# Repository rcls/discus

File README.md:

Discus is an 8-bit CPU built from discrete transistors.
[Refer to the website for documentation](http://rcls.github.io/discus)

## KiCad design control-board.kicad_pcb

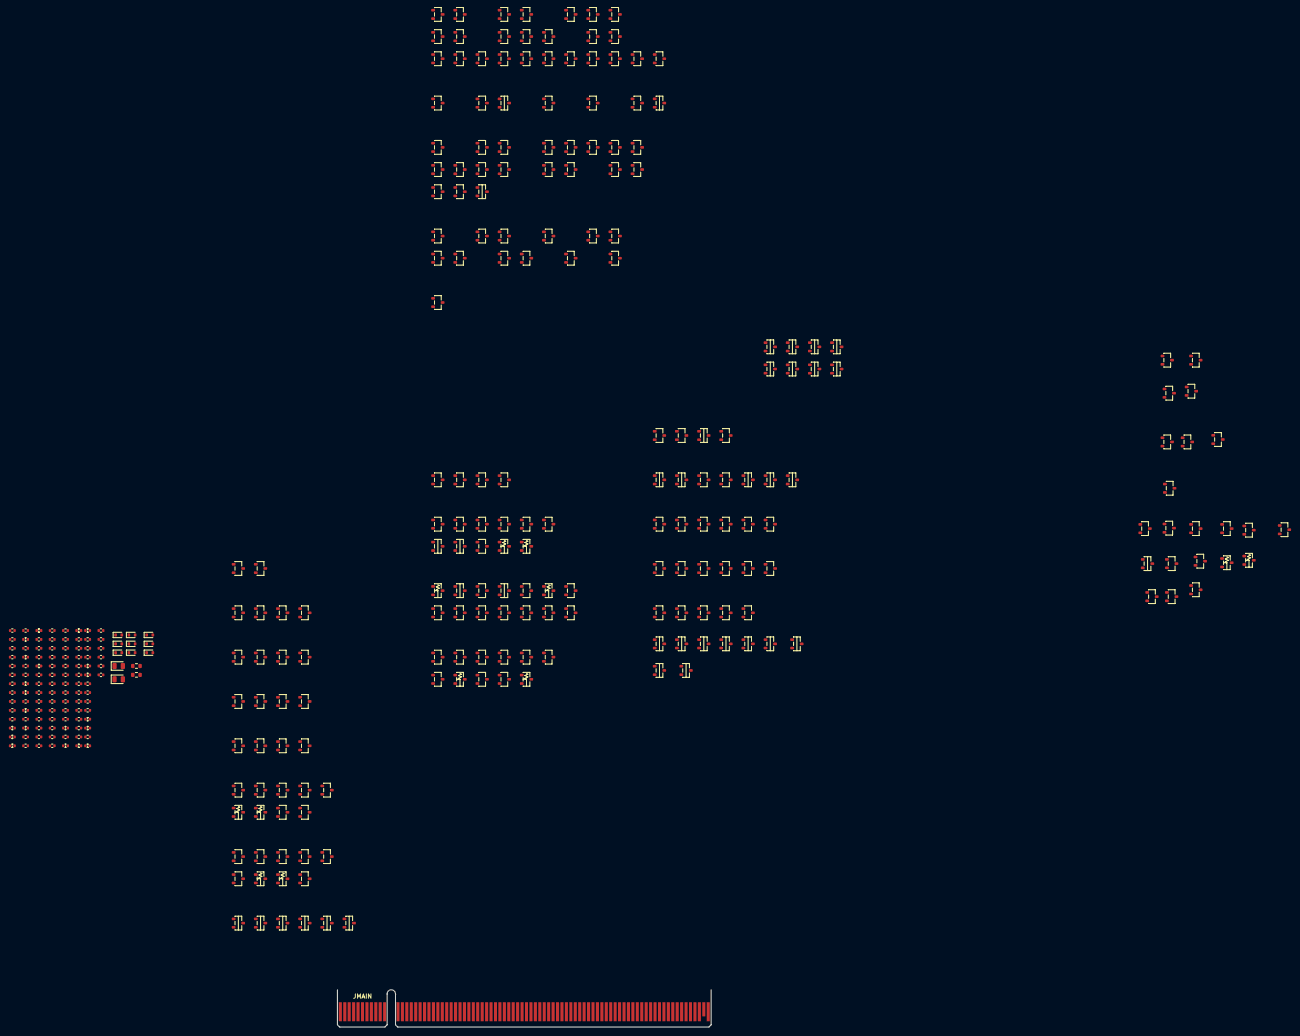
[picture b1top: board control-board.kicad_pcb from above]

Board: 4 copper layers, 331 parts (0 on the bottom side), 182 nets, no tracks yet.

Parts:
D0DS, D0W, D1DS, D1W, D2DS, D2W, D3DS, D3W, D4W: RB751S40; SOD523
D1: ledgreen; 0805-diode
D2: ledred; 0805-diode
JMAIN: unknown; BUS_PCIexpress_x16
M0DS, M0R, M0W, M1BJ, M1BK, M1DS, M1P, M1R, M1W, M2DS, M2N2, M2N4D, M2N7D, M2NP, M2P, M2PP, M2R, M2W, M3BJ, M3BK, M3DS, M3R, M3U6, M3W, M4DS, M4R, M4W, M5DS, M5R, M5W, M6R, M6W, M7R, M7W, M8W: NX3008PBK; SOT23_pmos
M1A1D, M1A2D, M1A3D, M1A4D, M1A5D, M1A6D, M1D, M1G, M1H, M1L2D, M1L4D, M1L5D, M1L6D, M1MAC, M1MAJ, M1MAK, M1MU5, M1MW1, M1MW2, M1N2, M1N4D, M1N7D, M1NAC, M1NAF0S, M1NAF1S, M1NAJ, M1NAK, M1NP, M1NU5, M1NW0, M1NW1, M1NW2, M1OL0S, M1OL1S, M1OU0S, M1OU1S, M1PP, M1S2D, M1S3D, M1S4D, M1S5D, M1S6D, M1S7D, M1U1, M1U2, M1U3, M1U6, M1U7, M2A1D, M2A2D, M2A3D, M2A4D, M2A5D, M2A6D, M2BJ, M2BK, M2D, M2G, M2H, M2L2D, M2L4D, M2L5D, M2L6D, M2MAC, M2MAJ, M2MAK, M2MU5, M2MW1, M2MW2, M2NAC, M2NAF0S, M2NAF1S, M2NAJ, M2NAK, M2NU5, M2NW0, M2NW1, M2NW2, M2OL0S, M2OL1S, M2OU0S, M2OU1S, M2S2D, M2S3D, M2S4D, M2S5D, M2S6D, M2S7D, M2U1, M2U2, M2U3, M2U6, M2U7, M3A2D, M3A5D, M3D, M3MAC, M3NAC, M3OU0S, M3OU1S, M3S3D, M3S4D, M3U3, M3U7, M4BJ, M4BK, M4D, M4S3D, M4S4D, M5D, M5S3D, M6D, M7D, M8D, M9D, M10D, M11D: FDV301N; SOT23_nmos
MAF0S, MAF1S: FDV301N; SOT23_nmos
MCD: FDV301N; SOT23_nmos
MIAC: FDV301N; SOT23_nmos
MIAF0S, MIAF1S: FDV301N; SOT23_nmos
MIAJ: FDV301N; SOT23_nmos
MIAK: FDV301N; SOT23_nmos
MIBC: FDV301N; SOT23_nmos
MIBF0S, MIBF1S: FDV301N; SOT23_nmos
MIP: NX3008PBK; SOT23_pmos
MIU5: FDV301N; SOT23_nmos
MIW0, MIW1, MIW2: FDV301N; SOT23_nmos
MJAC: FDV301N; SOT23_nmos
MJAF0S, MJAF1S: FDV301N; SOT23_nmos
MJAJ: FDV301N; SOT23_nmos
MJAK: FDV301N; SOT23_nmos
MJBC: FDV301N; SOT23_nmos
MJBF0S, MJBF1S: FDV301N; SOT23_nmos
MJU5: FDV301N; SOT23_nmos
MJW0, MJW1, MJW2: FDV301N; SOT23_nmos
ML0S, ML1D, ML1S, ML3D, ML7D, ML8D: FDV301N; SOT23_nmos
MN0, MN0S, MN1, MN1S, MN3D, MN5D, MN6D: FDV301N; SOT23_nmos
MNL0S, MNL1S: FDV301N; SOT23_nmos
MNU0S, MNU1S: FDV301N; SOT23_nmos
MS1D: FDV301N; SOT23_nmos
MS8D: NX3008PBK; SOT23_pmos
MU4: FDV301N; SOT23_nmos
MW0: FDV301N; SOT23_nmos
Q1BC, Q1BF0S, Q1BF1S, Q1BJ, Q1BK, Q1U6, Q2BC, Q2BF0S, Q2BF1S, Q2BJ, Q2BK, Q2U6: PDTC124TU; SOT23_bias
R0, R0DS, R0R, R0W, R1, R1DS, R1R, R1U6, R1W, R2, R2DS, R2R, R2U6, R2W, R3, R3DS, R3R, R3W, R4, R4R, R4W, R5, R6, R7: 2k49; R_0402_load
R1BJ, R1BK, R1D, R1P, R1S3D, R2BJ, R2BK, R2P, R2S3D, R3D, R4D: 820; R_0402_strong
R8, R9: 1k5; 0603
RA1D, RA2D, RA4D, RA6D: 2k49; R_0402_load
RCD: 2k49; R_0402_load
RG: 2k49; R_0402_load
RH: 2k49; R_0402_load
RIAC: 2k49; R_0402_load
RIAF0S, RIAF1S: 2k49; R_0402_load
RIAJ: 2k49; R_0402_load
RIAK: 2k49; R_0402_load
RIBC: 2k49; R_0402_load
RIBF0S, RIBF1S: 2k49; R_0402_load
RIP: 2k49; R_0402_load
RIU5: 2k49; R_0402_load
RIW0, RIW1, RIW2: 2k49; R_0402_load
RJAC: 2k49; R_0402_load
RJAF0S, RJAF1S: 2k49; R_0402_load
RJAJ: 2k49; R_0402_load
RJAK: 2k49; R_0402_load
RJBC: 2k49; R_0402_load
RJBF0S, RJBF1S: 2k49; R_0402_load
RJU5: 2k49; R_0402_load
RJW0, RJW1, RJW2: 2k49; R_0402_load
RL0S, RL1S, RL2D: 820; R_0402_strong
RL1D, RL3D, RL4D, RL7D, RL8D: 2k49; R_0402_load
RMAC: 2k49; R_0402_load
RMAJ: 2k49; R_0402_load
RMAK: 2k49; R_0402_load
RMU5: 2k49; R_0402_load
RMW1, RMW2: 2k49; R_0402_load
RN0, RN1, RN3D, RN5D, RN6D: 2k49; R_0402_load
RN0S, RN1S: 820; R_0402_strong
RNL0S, RNL1S: 820; R_0402_strong
RNU0S, RNU1S: 2k49; R_0402_load
ROU0S, ROU1S: 2k49; R_0402_load
RS1D, RS5D, RS7D: 820; R_0402_strong
RS6D, RS8D: 2k49; R_0402_load
RU1, RU2, RU3, RU4, RU7: 2k49; R_0402_load

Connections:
AND: JMAIN.B60, M1A2D.3 (D), M1N7D.1 (G), M2A2D.3 (D), M2N7D.1 (G), M3A2D.3 (D), RA2D.1
AR#: JMAIN.B58, M1N4D.3 (D), M2N4D.3 (D)
AS: JMAIN.B59, M1A3D.3 (D), M2A3D.3 (D)
BK: M1BK.3 (D), M2BK.3 (D), M6R.1 (G), R1BK.1
BK#: M3BK.3 (D), M4BK.3 (D), M7R.1 (G), R2BK.2
Bling: D1.2, D2.2, JMAIN.B67
CON: JMAIN.B53, M1U2.1 (G), M1U3.3 (D), M2U3.3 (D), M3U3.3 (D), MU4.2 (S), RU3.1
CR: JMAIN.B55, M11D.3 (D)
CR#_D: M1A4D.1 (G), M1A6D.3 (D), M11D.1 (G), RA6D.1
CS#: JMAIN.B56, M1N7D.3 (D), M2N7D.3 (D)
CW#: M3MAC.1 (G), M3NAC.1 (G), MCD.3 (D), RCD.1
Ci#: JMAIN.B7, M1MAC.1 (G)
Co: M3D.1 (G), MIBC.1 (G), MJBC.3 (D), Q1BC.3, RJBC.1
Co#: M2S2D.1 (G), MIBC.3 (D), MJBC.1 (G), Q2BC.3, R8.1, RIBC.1
CoE#: JMAIN.B57, M1D.3 (D), M2D.3 (D), M8D.3 (D), R3D.1
Cond#_D: M1S5D.1 (G), M3S3D.3 (D), M4S4D.1 (G), R2S3D.1
D#_A_C: M1MAC.3 (D), M1NAC.1 (G), M2MAC.3 (D), M3MAC.3 (D), MIAC.2 (S), RMAC.1
D#_A_J: M1MAJ.3 (D), M1NAJ.1 (G), M2MAJ.3 (D), MIAJ.2 (S), RMAJ.1
D#_A_K: M1MAK.3 (D), M1NAK.1 (G), M2MAK.3 (D), MIAK.2 (S), RMAK.1
D#_U5: M1MU5.3 (D), M1NU5.1 (G), M2MU5.3 (D), MIU5.2 (S), RMU5.1
D#_W1: M1MW1.3 (D), M1NW1.1 (G), M2MW1.3 (D), MIW1.2 (S), RMW1.1
D#_W2: M1MW2.3 (D), M1NW2.1 (G), M2MW2.3 (D), MIW2.2 (S), RMW2.1
Flag_D: M1S2D.3 (D), M1S3D.1 (G), M4S3D.1 (G), MS1D.3 (D), RS1D.1
GND: JMAIN.B34, M1A2D.2 (S), M1A3D.2 (S), M1A4D.2 (S), M1D.2 (S), M1L2D.2 (S), M1MAC.2 (S), M1MAJ.2 (S), M1MAK.2 (S), M1MU5.2 (S), M1MW1.2 (S), M1MW2.2 (S), M1N2.2 (S), M1N4D.2 (S), M1N7D.2 (S), M1NAC.2 (S), M1NAF0S.2 (S), M1NAF1S.2 (S), M1NAJ.2 (S), M1NAK.2 (S), M1NP.2 (S), M1NU5.2 (S), M1NW0.2 (S), M1NW1.2 (S), M1NW2.2 (S), M1OL0S.2 (S), M1OL1S.2 (S), M1OU0S.2 (S), M1OU1S.2 (S), M1PP.2 (S), M1S4D.2 (S), M1S5D.2 (S), M1S6D.2 (S), M1U1.2 (S), M1U3.2 (S), M1U6.2 (S), M1U7.2 (S), M2A2D.2 (S), M2A3D.2 (S), M2A4D.2 (S), M2BJ.2 (S), M2BK.2 (S), M2H.2 (S), M2L2D.2 (S), M2MAC.2 (S), M2MAJ.2 (S), M2MAK.2 (S), M2MU5.2 (S), M2MW1.2 (S), M2MW2.2 (S), M2NAC.2 (S), M2NAF0S.2 (S), M2NAF1S.2 (S), M2NAJ.2 (S), M2NAK.2 (S), M2NU5.2 (S), M2NW0.2 (S), M2NW1.2 (S), M2NW2.2 (S), M2OL0S.2 (S), M2OL1S.2 (S), M2OU0S.2 (S), M2OU1S.2 (S), M2S2D.2 (S), M2S3D.2 (S), M2S4D.2 (S), M2S5D.2 (S), M2S6D.2 (S), M2S7D.2 (S), M2U1.2 (S), M2U2.2 (S), M2U3.2 (S), M2U6.2 (S), M2U7.2 (S), M3A2D.2 (S), M3MAC.2 (S), M3NAC.2 (S), M3S4D.2 (S), M3U3.2 (S), M4BJ.2 (S)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
I0: JMAIN.B17, M0R.1 (G), M2R.1 (G)
I0#: JMAIN.B18, M1R.1 (G), M3R.1 (G)
I1: JMAIN.B19, M4R.1 (G)
I1#: JMAIN.B20, M5R.1 (G)
I2: JMAIN.B21, M1A1D.1 (G), M1A5D.1 (G), M1L4D.1 (G), M8D.1 (G)
I2#: JMAIN.B22, M1A2D.1 (G), M1A3D.1 (G), M1A6D.1 (G), M5D.1 (G)
I3: JMAIN.B23, M2L4D.1 (G)
I3#: JMAIN.B24, M1L2D.1 (G), M2A2D.1 (G), M2A5D.1 (G), M2A6D.2 (S), M2D.1 (G), ML1D.1 (G), ML7D.1 (G)
I4: JMAIN.B25, M2A4D.1 (G), M4D.1 (G), ML8D.1 (G)
I4#: JMAIN.B26, M1G.1 (G), M9D.1 (G), ML3D.1 (G)
I5: JMAIN.B27, M1L6D.1 (G), M1MW1.1 (G)
I5#: JMAIN.B28, M1U7.1 (G), M2L5D.2 (S)
I6: JMAIN.B29, M1L5D.1 (G), M1U3.1 (G), M2U7.1 (G), M3A5D.2 (S), M6D.1 (G)
I6#: JMAIN.B30, M1L6D.2 (S), M2A1D.1 (G), M2A3D.1 (G), M2G.1 (G), M2L6D.2 (S), M7D.1 (G), M10D.1 (G), MCD.1 (G)
I7: JMAIN.B31, M2L6D.1 (G), M2U3.1 (G), M3U7.1 (G)
I7#: JMAIN.B32, M2L5D.1 (G), MCD.2 (S), MN5D.2 (S)
IJ: JMAIN.B68, M1A1D.2 (S), M1D.1 (G), M2A1D.2 (S), M3A2D.1 (G), M3BJ.3 (D), M3U3.1 (G), M4BJ.3 (D), MN6D.2 (S), R2BJ.2
IJ#: M1BJ.3 (D), M2A6D.1 (G), M2BJ.3 (D), M2H.1 (G), M3A5D.1 (G), M6R.2 (S), M7R.2 (S), R1BJ.1, R9.1
IN#: JMAIN.B63, ML7D.3 (D), RL7D.1
Inc: JMAIN.B1, M1S6D.3 (D), M2S6D.3 (D), RS6D.1
Jump: JMAIN.B2, M1S5D.3 (D), M1S7D.1 (G), M2S5D.3 (D), M2S6D.1 (G), RS5D.1
K6#: JMAIN.B51, MN0.3 (D), RN0.1
K7#: JMAIN.B52, MN1.3 (D), RN1.1
MPre#: ML7D.2 (S), ML8D.3 (D), MU4.1 (G), RL8D.1
MR#: JMAIN.B66, M1L4D.3 (D), MN5D.1 (G), RL4D.1
MW: JMAIN.B65, M1L2D.3 (D), M2L2D.3 (D), RL2D.1
Misc#_D: M1L5D.3 (D), ML3D.2 (S), ML8D.2 (S)
N#: JMAIN.B62, M1A5D.3 (D), R4D.2
O0: JMAIN.B9, MN0.1 (G), R0.1
O1: JMAIN.B10, MN1.1 (G), R1.1
O2: JMAIN.B11, M2S3D.1 (G), M5S3D.1 (G), R2.1
O3: JMAIN.B12, MS1D.1 (G), R3.1
O4: JMAIN.B13, M1S2D.1 (G), R4.1
O5: JMAIN.B14, M1S4D.1 (G), M2S7D.1 (G), R5.1
O6: JMAIN.B15, M1U1.1 (G), MN3D.1 (G), R6.1
O6#_D: M2S4D.1 (G), MN3D.3 (D), RN3D.1
O7: JMAIN.B16, M2U1.1 (G), M3S4D.1 (G), R7.1
OJump#: M1MAJ.1 (G), M1U2.3 (D), M2S5D.1 (G), RU2.1
OR: JMAIN.B61, M1A4D.3 (D), M2A4D.3 (D), RA4D.1
OUT#: JMAIN.B64, ML1D.3 (D), RL1D.1
P0#_S: M2OL0S.1 (G), MIBF0S.1 (G), MJBF0S.3 (D), Q1BF0S.3, RJBF0S.1
P0_S: MIBF0S.3 (D), MJBF0S.1 (G), MNL1S.2 (S), Q2BF0S.3, RIBF0S.1
P1#_S: M2OL1S.1 (G), MIBF1S.1 (G), MJBF1S.3 (D), MNL0S.2 (S), Q1BF1S.3, RJBF1S.1
P1_S: MIBF1S.3 (D), MJBF1S.1 (G), Q2BF1S.3, RIBF1S.1
PRE: M1MAK.1 (G), MU4.3 (D), RU4.1
Push#: M1S7D.3 (D), M2OU0S.1 (G), M2OU1S.1 (G), MNU0S.1 (G), MNU1S.1 (G), MS8D.1 (G), RS7D.1
Q0#_S: M1DS.1 (G), M1OU1S.1 (G), M3DS.1 (G), MN0S.3 (D), MNU0S.2 (S), RN0S.1
Q0_S: M0DS.1 (G), M2DS.1 (G), ML0S.3 (D), MN0S.1 (G), RL0S.1
Q1#_S: M5DS.1 (G), MN1S.3 (D), MNU1S.2 (S), RN1S.1
Q1_S: M1OU0S.1 (G), M4DS.1 (G), ML1S.3 (D), MN1S.1 (G), RL1S.1
QE: JMAIN.B54, MN6D.3 (D), RN6D.1
Q_A1_D: M1A1D.3 (D), M1N4D.1 (G), M2A1D.3 (D), M2N4D.1 (G), RA1D.1
Q_G: M1G.3 (D), M1H.1 (G), M2G.3 (D), RG.1
Q_H: M1H.3 (D), M1NW0.1 (G), MIW0.2 (S), MW0.3 (D), RH.1
Q_I_P: M1P.1 (G), MIP.3 (D), RIP.2
Q_L6_D: M1L6D.3 (D), M2L4D.2 (S), M2L6D.3 (D)
Q_N5_D: MN5D.3 (D), MN6D.1 (G), RN5D.1
Q_N_L0_S: ML0S.1 (G), MNL0S.3 (D), RNL0S.1
Q_N_L1_S: ML1S.1 (G), MNL1S.3 (D), RNL1S.1
Q_O_L0_S: M1OL0S.3 (D), M2OL0S.3 (D), ML0S.2 (S)
Q_O_L1_S: M1OL1S.3 (D), M2OL1S.3 (D), ML1S.2 (S)
Q_U1: M1U1.3 (D), M2U1.3 (D), M2U2.1 (G), RU1.1
R0_S: M1NAF0S.1 (G), M3OU0S.3 (D), MAF0S.3 (D), MIAF0S.2 (S), ROU0S.1
R1_S: M1NAF1S.1 (G), M3OU1S.3 (D), MAF1S.3 (D), MIAF1S.2 (S), ROU1S.1
RA: JMAIN.B39, M0R.3 (D), R0R.2
RK: JMAIN.B43, M7R.3 (D), R4R.2
RST#: JMAIN.B8, M1MU5.1 (G)
RU: JMAIN.B42, M3R.3 (D), R3R.2
RX: JMAIN.B40, M1R.3 (D), R1R.2
RY: JMAIN.B41, M2R.3 (D), R2R.2
R_C: MIAC.3 (D), MJAC.1 (G), Q1BC.2, RIAC.1
R_F0_S: MIAF0S.1 (G), MJAF0S.3 (D), Q1BF0S.2, RJAF0S.1
R_F1_S: MIAF1S.1 (G), MJAF1S.3 (D), Q1BF1S.2, RJAF1S.1
R_J: MIAJ.3 (D), MJAJ.1 (G), Q1BJ.2, RIAJ.1
R_K: MIAK.3 (D), MJAK.1 (G), Q1BK.2, RIAK.1
Ret: JMAIN.B3, M1OL0S.1 (G), M1OL1S.1 (G), M1S4D.3 (D), M1S6D.1 (G), M2S4D.3 (D), M3S4D.3 (D), M4S4D.3 (D), MNL0S.1 (G), MNL1S.1 (G), R1D.2
S0: D0DS.2, JMAIN.B35, M0DS.3 (D), R0DS.2
S1: D1DS.2, JMAIN.B36, M1DS.3 (D), R1DS.2
S2: D3DS.2, JMAIN.B37, M3DS.3 (D), R3DS.2
S3: D2DS.2, JMAIN.B38, M2DS.3 (D), R2DS.2
S#_P: M1PP.1 (G), M2P.3 (D), M2PP.1 (G), R2P.1
SO#_D: M2L2D.1 (G), ML1D.2 (S), ML3D.3 (D), RL3D.1
S_C: MIAC.1 (G), MJAC.3 (D), Q2BC.2, RJAC.1
S_F0_S: MIAF0S.3 (D), MJAF0S.1 (G), Q2BF0S.2, RIAF0S.1
S_F1_S: MIAF1S.3 (D), MJAF1S.1 (G), Q2BF1S.2, RIAF1S.1
S_J: MIAJ.1 (G), MJAJ.3 (D), Q2BJ.2, RJAJ.1
S_K: MIAK.1 (G), MJAK.3 (D), Q2BK.2, RJAK.1
S_P: M1NP.1 (G), M1P.3 (D), M2NP.1 (G), R1P.1
VPush: JMAIN.B4, MS8D.3 (D), RS8D.2
Vdd: JMAIN.B33, M1BJ.2 (S), M1BK.2 (S), M1P.2 (S), M2N2.2 (S), M2N4D.2 (S), M2N7D.2 (S), M2NP.2 (S), M2P.2 (S), M2PP.2 (S), M3BJ.2 (S), M3BK.2 (S), M3U6.2 (S), MIP.2 (S), R1D.1, R1S3D.2, R1U6.2, R2S3D.2, R3D.2, R4D.1, RA1D.2, RA2D.2, RA4D.2, RA6D.2, RCD.2, RG.2, RH.2, RIAC.2, RIAF0S.2, RIAF1S.2, RIAJ.2, RIAK.2, RIBC.2, RIBF0S.2, RIBF1S.2, RIU5.2, RIW0.2, RIW1.2, RIW2.2, RJAC.2, RJAF0S.2, RJAF1S.2, RJAJ.2, RJAK.2, RJBC.2, RJBF0S.2, RJBF1S.2, RJU5.2, RJW0.2, RJW1.2, RJW2.2, RL0S.2, RL1D.2, RL1S.2, RL2D.2, RL3D.2, RL4D.2, RL7D.2, RL8D.2, RMAC.2, RMAJ.2, RMAK.2, RMU5.2, RMW1.2, RMW2.2, RN0.2, RN0S.2, RN1.2, RN1S.2, RN3D.2, RN5D.2, RN6D.2, RNL0S.2, RNL1S.2, RNU0S.2, RNU1S.2, ROU0S.2, ROU1S.2, RS1D.2, RS5D.2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
W0: M0W.1 (G), M2W.1 (G), M8W.1 (G), MIW0.1 (G), MJW0.3 (D), RJW0.1
W0#: M1W.1 (G), M3W.1 (G), MIW0.3 (D), MJW0.1 (G), RIW0.1
W1: M4W.1 (G), MIW1.1 (G), MJW1.3 (D), RJW1.1
W1#: M5W.1 (G), MIW1.3 (D), MJW1.1 (G), RIW1.1
W2: M6W.1 (G), MIW2.1 (G), MJW2.3 (D), RJW2.1
W2#: M7W.1 (G), MIW2.3 (D), MJW2.1 (G), RIW2.1
WA: D0W.2, JMAIN.B44, M0W.3 (D), R0W.2
WR: D4W.2, JMAIN.B69, M8W.3 (D), R4W.2
WU: D3W.2, JMAIN.B47, M3W.3 (D), R3W.2
WX: D1W.2, JMAIN.B45, M1W.3 (D), R1W.2
WY: D2W.2, JMAIN.B46, M2W.3 (D), R2W.2
X_A5_D: M1A5D.2 (S), M2A5D.3 (D)
X_A_C: M1NAC.3 (D), M2NAC.3 (D), M3NAC.3 (D), MJAC.2 (S)
X_A_F0_S: M1NAF0S.3 (D), M2NAF0S.3 (D), MJAF0S.2 (S)
X_A_F1_S: M1NAF1S.3 (D), M2NAF1S.3 (D), MJAF1S.2 (S)
X_A_J: M1NAJ.3 (D), M2NAJ.3 (D), MJAJ.2 (S)
X_A_K: M1NAK.3 (D), M2NAK.3 (D), MJAK.2 (S)
X_S3_D: M1S3D.2 (S), M2S3D.3 (D)
X_U5: M1NU5.3 (D), M2NU5.3 (D), MJU5.2 (S)
X_W0: M1NW0.3 (D), M2NW0.3 (D), MJW0.2 (S)
X_W1: M1NW1.3 (D), M2NW1.3 (D), MJW1.2 (S)
X_W2: M1NW2.3 (D), M2NW2.3 (D), MJW2.2 (S)
Y_A5_D: M2A5D.2 (S), M3A5D.3 (D)
Y_S3_D: M1S3D.3 (D), M3S3D.1 (G), R1S3D.1
Z: JMAIN.B6, MS1D.2 (S)
Z_S3_D: M3S3D.2 (S), M4S3D.3 (D), M5S3D.3 (D)
_co1_D: M2D.2 (S), M3D.3 (D), M6D.3 (D)
_co2_D: M9D.2 (S), M10D.3 (D)
_co3_D: M8D.2 (S), M9D.3 (D)
_co4_D: M3D.2 (S), M4D.3 (D)
_co6_D: M4D.2 (S), M5D.3 (D), M6D.2 (S), M7D.3 (D)
g#_B_J: M1BJ.1 (G), M2BJ.1 (G), Q1BJ.3, R2BJ.1
g#_B_K: M1BK.1 (G), M2BK.1 (G), Q1BK.3, R2BK.1
g_B_J: M3BJ.1 (G), M4BJ.1 (G), Q2BJ.3, R1BJ.2
g_B_K: M3BK.1 (G), M4BK.1 (G), Q2BK.3, R1BK.2
g_U6: M1U6.1 (G), Q1U6.3, R2U6.1
iRST: M1U6.3 (D), M2U6.1 (G), M3U6.1 (G), Q2U6.3, R1U6.1
iRST#: M2U6.3 (D), M3U6.3 (D), R0.2, R1.2, R2.2, R2U6.2, R3.2, R4.2, R5.2, R6.2, R7.2, RU2.2
lR: MIU5.3 (D), MJU5.1 (G), Q2U6.2, RIU5.1
lR#: MIU5.1 (G), MJU5.3 (D), Q1U6.2, RJU5.1
phi: D0W.1, D1W.1, D2W.1, D3W.1, D4W.1, JMAIN.B48, M1N2.1 (G), M1PP.3 (D), M2MAC.1 (G), M2MAJ.1 (G), M2MAK.1 (G), M2MU5.1 (G), M2MW1.1 (G), M2MW2.1 (G), M2N2.1 (G), M2NAC.1 (G), M2NAF0S.1 (G), M2NAF1S.1 (G), M2NAJ.1 (G), M2NAK.1 (G), M2NU5.1 (G), M2NW0.1 (G), M2NW1.1 (G), M2NW2.1 (G), M2PP.3 (D), M6W.2 (S), M7W.2 (S), MAF0S.1 (G), MAF1S.1 (G), MW0.1 (G), Q1BC.1, Q1BF0S.1, Q1BF1S.1, Q1BJ.1, Q1BK.1, Q1U6.1, Q2BC.1, Q2BF0S.1, Q2BF1S.1, Q2BJ.1, Q2BK.1, Q2U6.1, R1P.2
phi1: JMAIN.B50, M1NP.3 (D), M2NP.3 (D), MS8D.2 (S), R2P.2
phi#: D0DS.1, D1DS.1, D2DS.1, D3DS.1, M1N2.3 (D), M2N2.3 (D), M4DS.2 (S), M5DS.2 (S)
t_W: M0W.2 (S), M1W.2 (S), M4W.3 (D)
unnamed_net1: D1.1, R8.2
unnamed_net2: D2.1, R9.2
v_W: M2W.2 (S), M3W.2 (S), M5W.3 (D)
w2n: M1G.2 (S), M1MW2.1 (G), M2G.2 (S), M3U7.3 (D), RU7.1
w_W: M4W.2 (S), M5W.2 (S), M6W.3 (D)
x_A6_D: M1A6D.2 (S), M2A6D.3 (D)
x_D_S: M0DS.2 (S), M1DS.2 (S), M4DS.3 (D)
x_H: M1H.2 (S), M2H.3 (D)
x_L4_D: M1L4D.2 (S), M2L4D.3 (D)
x_L5_D: M1L5D.2 (S), M2L5D.3 (D)
x_O_U0_S: M1OU0S.3 (D), M2OU0S.3 (D), M3OU0S.2 (S)
x_O_U1_S: M1OU1S.3 (D), M2OU1S.3 (D), M3OU1S.2 (S)
x_R: M0R.2 (S), M1R.2 (S), M4R.3 (D)
x_S2_D: M1S2D.2 (S), M2S2D.3 (D)
x_S7_D: M1S7D.2 (S), M2S7D.3 (D)
x_U0_S: M3OU0S.1 (G), MNU0S.3 (D), RNU0S.1
x_U1_S: M3OU1S.1 (G), MNU1S.3 (D), RNU1S.1
x_U2: M1U2.2 (S), M2U2.3 (D)
x_U7: M1U7.3 (D), M2U7.3 (D), M3U7.2 (S)
y_D_S: M2DS.2 (S), M3DS.2 (S), M5DS.3 (D)
y_R: M2R.2 (S), M3R.2 (S), M5R.3 (D)
z_R: M4R.2 (S), M5R.2 (S), M6R.3 (D)
z_W: M7W.3 (D), M8W.2 (S)
ϕin: JMAIN.B5, M2P.1 (G), MIP.1 (G)

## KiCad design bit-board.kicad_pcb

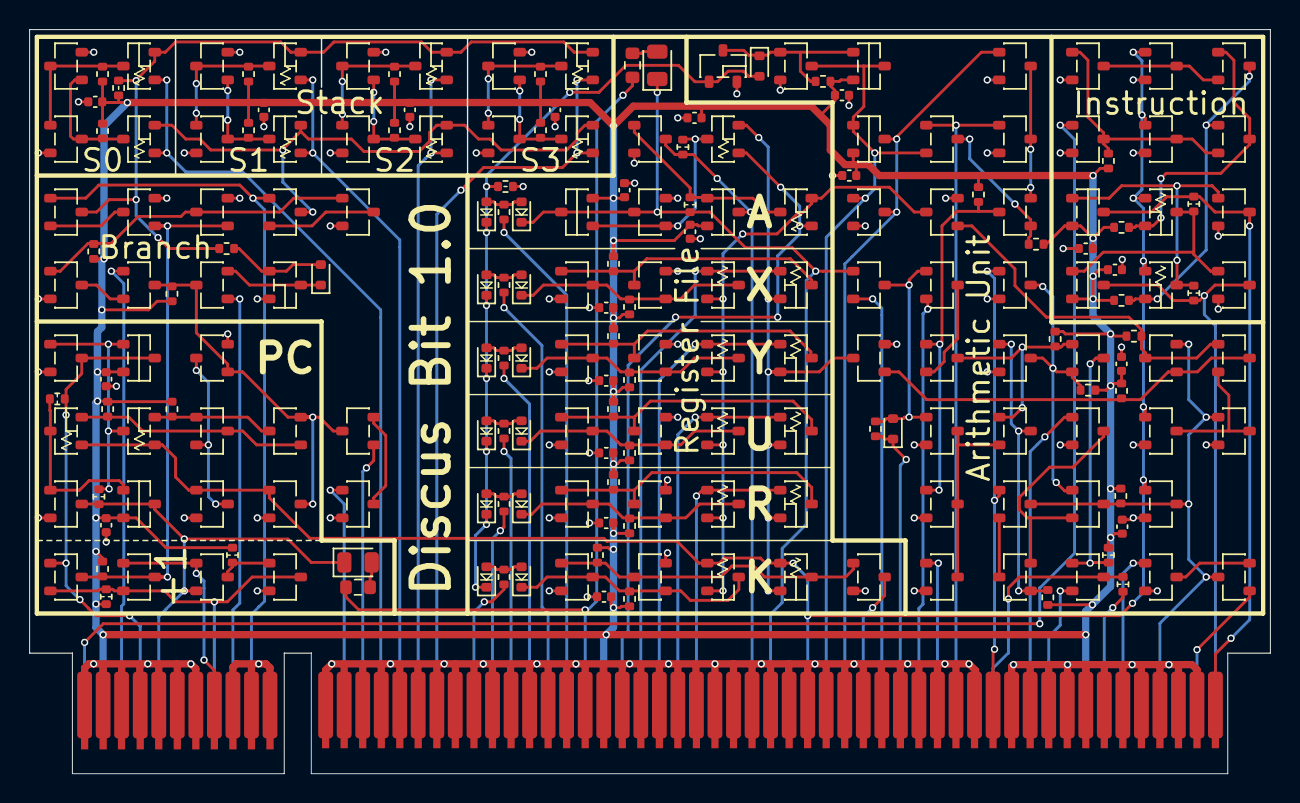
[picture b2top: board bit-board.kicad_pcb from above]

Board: 4 copper layers, 85.0 x 51.0 mm, 209 parts (0 on the bottom side), 120 nets.

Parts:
C1, C2, C3, C4, C5, C6, C7, C8, C9, C10, C11, C12, C13, C14, C15, C16, C17, C18, C19, C20: 0.1u; C_0402
D1, D4, D5: RB751S40; SOD523
D1A, D1K, D1R, D1U, D1X, D1Y, D2A, D2K, D2R, D2U, D2X, D2Y: 1N4148WT; SOD523-diode
D2: ledgreen; 0805-diode
D3: ledred; 0805-diode
JMAIN: unknown; pci-edge-3v
M1, M1B2, M1B3, M1DE, M1L0, M1L1, M1L2, M1L3, M1MAG, M1NAF, M1NAG, M1NEE, M1NL, M1NS4, M1OEE, M1ON, M1S5, M1S6, M1S7, M1S8, M1S9, M1XE, M2, M2A, M2BF, M2BG, M2DE, M2L0, M2L1, M2L2, M2L3, M2MAG, M2NAF, M2NAG, M2NEE, M2NL, M2NS4, M2OEE, M2ON, M2S5, M2S6, M2S7, M2S8, M2S9, M2XE, M3, M3OEE, M3ON, M3XE, M4, M4A, M4BF, M4BG, M4XE: FDV301N; SOT23_nmos
M1A, M1BF, M1BG, M2B2, M2B3, M3A, M3BF, M3BG: NX3008PBK; SOT23_pmos
MAF: FDV301N; SOT23_nmos
ME: FDV301N; SOT23_nmos
MI3, MI5: FDV301N; SOT23_nmos
MIAF: FDV301N; SOT23_nmos
MIAG: FDV301N; SOT23_nmos
MIE: FDV301N; SOT23_nmos
MIK: FDV301N; SOT23_nmos
MIL: FDV301N; SOT23_nmos
MIR: FDV301N; SOT23_nmos
MIS4: FDV301N; SOT23_nmos
MIU: FDV301N; SOT23_nmos
MIX: FDV301N; SOT23_nmos
MIY: FDV301N; SOT23_nmos
MJAF: FDV301N; SOT23_nmos
MJAG: FDV301N; SOT23_nmos
MJK: FDV301N; SOT23_nmos
MJL: FDV301N; SOT23_nmos
MJR: FDV301N; SOT23_nmos
MJU: FDV301N; SOT23_nmos
MJX: FDV301N; SOT23_nmos
MJY: FDV301N; SOT23_nmos
ML: FDV301N; SOT23_nmos
MNN: FDV301N; SOT23_nmos
MPE: FDV301N; SOT23_nmos
MPS4: FDV301N; SOT23_nmos
Q1BF, Q1BG, Q1K, Q1L0, Q1L1, Q1L2, Q1L3, Q1R, Q1U, Q1X, Q1Y, Q2A, Q2BF, Q2BG, Q2K, Q2L0, Q2L1, Q2L2, Q2L3, Q2R, Q2U, Q2X, Q2Y, Q3A: PDTC124TU; SOT23_bias
Q3: BC847BW; SOT23_bjt
QI4: BC847BW; SOT23_bjt
R1: 10k; R_0402_pull
R1A, R1BF, R1BG, R2A, R2BF, R2BG: 820; R_0402_strong
R1K, R1L0, R1L1, R1L2, R1L3, R1R, R1U, R1X, R1Y, R2L0, R2L1, R2L2, R2L3, R3A, R6: 2k49; R_0402_load
R2: 47k; R_0402_pull
R4, R5: 1k5; 0603
RDE: 2k49; R_0402_load
RI3, RI4, RI5: 2k49; R_0402_load
RIAF: 2k49; R_0402_load
RIAG: 2k49; R_0402_load
RIE: 820; R_0402_strong
RIK: 2k49; R_0402_load
RIL: 2k49; R_0402_load
RIR: 2k49; R_0402_load
RIS4: 820; R_0402_strong
RIU: 2k49; R_0402_load
RIX: 2k49; R_0402_load
RIY: 2k49; R_0402_load
RJAF: 2k49; R_0402_load
RJAG: 2k49; R_0402_load
RJK: 2k49; R_0402_load
RJL: 2k49; R_0402_load
RJR: 2k49; R_0402_load
RJU: 2k49; R_0402_load
RJX: 2k49; R_0402_load
RJY: 2k49; R_0402_load
RMAG: 2k49; R_0402_load
RNEE: 2k49; R_0402_load
RNN: 2k49; R_0402_load
RNS4: 2k49; R_0402_load
ROEE: 2k49; R_0402_load
RON: 2k49; R_0402_load
RPE: 820; R_0402_strong
RPS4: 820; R_0402_strong
RS6: 2k49; R_0402_load
RXE: 2k49; R_0402_load

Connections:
AND: JMAIN.A47, M4XE.1 (G)
AR#: D1.1, JMAIN.A45, RI5.2
AS: JMAIN.A44, MI5.2 (S)
Ao: JMAIN.A37, M3A.3 (D), M4A.3 (D), R2A.2
Ao#: D2.1, D2A.1, JMAIN.A38, M1A.3 (D), M2A.3 (D), MI5.1 (G), R1A.1
B: JMAIN.A42, M1B3.3 (D), M1ON.1 (G), M2B3.3 (D)
B#: JMAIN.A41, M1B2.3 (D), M1B3.1 (G), M2B2.3 (D), M2B3.1 (G), MNN.2 (S)
Bi: D4.1, M1B2.1 (G), M2B2.1 (G), QI4.3, RI4.1
Bi#: D1A.1, D1K.1, D1R.1, D1U.1, D1X.1, D1Y.1, D4.2, QI4.1, R1.2
Bling: JMAIN.A28, R4.2, R5.2
C2_E: M1NEE.3 (D), M2NEE.3 (D), M2OEE.1 (G), MIE.2 (S), RNEE.1
CON: JMAIN.A57, M2S8.1 (G)
CR: JMAIN.A53, MPE.2 (S)
CS#: JMAIN.A56, RPE.2
Ci#: JMAIN.B50, M1OEE.1 (G), M2NEE.1 (G)
Co#: JMAIN.A50, MPE.3 (D), RPE.1
D#_A_G: M1MAG.3 (D), M1NAG.1 (G), M2MAG.3 (D), MIAG.2 (S), RMAG.1
EA: D1.2, M2DE.1 (G), M2XE.1 (G), MI5.3 (D), RI5.1
EB: M1DE.1 (G), M3ON.3 (D), M3XE.1 (G), RON.1
GND: C1.1, C2.1, C3.1, C4.1, C5.1, C6.1, C7.1, C8.1, C9.1, C10.1, C11.1, C12.1, C13.1, C14.1, C15.1, C16.1, C17.1, C18.1, C19.1, C20.1, JMAIN.B1, JMAIN.B2, JMAIN.B3, JMAIN.B4, JMAIN.B5, JMAIN.B6, JMAIN.B7, JMAIN.B9, JMAIN.B10, JMAIN.B11, JMAIN.B14, JMAIN.B15, JMAIN.B16, JMAIN.B17, JMAIN.B18, JMAIN.B19, JMAIN.B20, JMAIN.B21, JMAIN.B22, JMAIN.B23, JMAIN.B24, JMAIN.B25, JMAIN.B26, JMAIN.B27, JMAIN.B28, JMAIN.B29, JMAIN.B30, JMAIN.B31, JMAIN.B32, JMAIN.B33, JMAIN.B34, JMAIN.B35, JMAIN.B36, JMAIN.B37, JMAIN.B38, JMAIN.B39, JMAIN.B40, JMAIN.B41, JMAIN.B42, JMAIN.B43, JMAIN.B44, JMAIN.B45, JMAIN.B46, JMAIN.B47, JMAIN.B48, JMAIN.B49, JMAIN.B51, JMAIN.B52, JMAIN.B53, JMAIN.B54, JMAIN.B55, JMAIN.B56, JMAIN.B57, JMAIN.B58, JMAIN.B59, JMAIN.B60, JMAIN.B61, M1B2.2 (S), M1B3.2 (S), M1L0.2 (S)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
I: JMAIN.A62, M1BG.3 (D), M2BG.3 (D), R1BG.1
I#: JMAIN.B62, M3BG.3 (D), M4BG.3 (D), R2BG.2
Inc: JMAIN.A3, M1S6.1 (G)
J: JMAIN.A16, M1S7.1 (G)
Jump: JMAIN.A15, M2S7.1 (G)
K: M4.1 (G), MIK.1 (G), MJK.3 (D), Q2K.3, RJK.1
K#: JMAIN.A61, M1S8.1 (G)
L_K: D2K.1, MIK.3 (D), MJK.1 (G), Q1K.3, RIK.1
L_L0: M1L0.3 (D), M2L0.1 (G), Q1L0.3, R1L0.1
L_L1: M1L1.3 (D), M2L1.1 (G), Q1L1.3, R1L1.1
L_L2: M1L2.3 (D), M2L2.1 (G), Q1L2.3, R1L2.1
L_L3: M1L3.3 (D), M2L3.1 (G), Q1L3.3, R1L3.1
L_R: D2R.1, MIR.3 (D), MJR.1 (G), Q1R.3, RIR.1
L_U: D2U.1, MIU.3 (D), MJU.1 (G), Q1U.3, RIU.1
L_X: D2X.1, MIX.3 (D), MJX.1 (G), Q1X.3, RIX.1
L_Y: D2Y.1, MIY.3 (D), MJY.1 (G), Q1Y.3, RIY.1
N#: JMAIN.A48, M2ON.1 (G), MNN.1 (G)
O: JMAIN.A1, M1MAG.1 (G)
OR: JMAIN.A46, M2DE.2 (S)
P: JMAIN.A4, M1NS4.1 (G), M3BF.3 (D), M4BF.3 (D), R2BF.2
P#: D3.1, JMAIN.A5, M1BF.3 (D), M2BF.3 (D), MIS4.2 (S), R1BF.1
PCi: JMAIN.B8, M2NS4.1 (G), MIS4.1 (G)
PCo: JMAIN.A8, M1NS4.2 (S), M2NS4.2 (S), MPS4.3 (D), RPS4.1
Pn#: M1.3 (D), M1NAF.1 (G), M1S6.3 (D), M1S7.3 (D), MAF.3 (D), MIAF.2 (S), RS6.1
Pp: M2S6.1 (G), M2S9.1 (G), MI3.3 (D), RI3.1
Pp#: M1NS4.3 (D), M2NS4.3 (D), M2S5.1 (G), MI3.1 (G), RNS4.1
Q: JMAIN.A59, M1NL.1 (G), M1OEE.3 (D), M1S8.3 (D), M2OEE.3 (D), MIL.2 (S), ML.3 (D), ROEE.1
QE: JMAIN.A52, ME.1 (G)
Q_D_E: M1DE.3 (D), M1XE.1 (G), MIE.1 (G), RDE.1
Q_I_E: MIE.3 (D), MPE.1 (G), RIE.1
Q_I_S4: MIS4.3 (D), MPS4.1 (G), RIS4.1
Q_X_E: M1NEE.1 (G), M1XE.3 (D), M3OEE.1 (G), RXE.1
RA: JMAIN.A27, R3A.1
RK: JMAIN.A22, R1K.1
RR: JMAIN.A23, R1R.1
RU: JMAIN.A24, R1U.1
RX: JMAIN.A26, R1X.1
RY: JMAIN.A25, R1Y.1
R_F: MIAF.1 (G), MJAF.3 (D), Q1BF.2, RJAF.1
R_G: MIAG.3 (D), MJAG.1 (G), Q1BG.2, RIAG.1
R_L0: M1L0.1 (G), M2L0.3 (D), Q2L0.3, R2L0.1
R_L1: M1L1.1 (G), M2L1.3 (D), Q2L1.3, R2L1.1
R_L2: M1L2.1 (G), M2L2.3 (D), Q2L2.3, R2L2.1
R_L3: M1L3.1 (G), M2L3.3 (D), Q2L3.3, R2L3.1
R_R: MIR.1 (G), MJR.3 (D), Q2R.3, RJR.1
R_U: MIU.1 (G), MJU.3 (D), Q2U.3, RJU.1
R_X: MIX.1 (G), MJX.3 (D), Q2X.3, RJX.1
R_Y: MIY.1 (G), MJY.3 (D), Q2Y.3, RJY.1
Ret: JMAIN.A9, M1.1 (G)
S0: JMAIN.A17, Q1L0.1, Q2L0.1
S1: JMAIN.A18, Q1L1.1, Q2L1.1
S2: JMAIN.A19, Q1L2.1, Q2L2.1
S3: JMAIN.A20, Q1L3.1, Q2L3.1
SB: M1S5.3 (D), Q1L0.2, Q1L1.2, Q1L2.2, Q1L3.2, R2.1, R6.2
SB#: M1S9.3 (D), Q2L0.2, Q2L1.2, Q2L2.2, Q2L3.2
S_F: MIAF.3 (D), MJAF.1 (G), Q2BF.2, RIAF.1
S_G: MIAG.1 (G), MJAG.3 (D), Q2BG.2, RJAG.1
VPush: JMAIN.A10, M1S5.1 (G), M1S9.1 (G)
Vdd: C1.2, C2.2, C3.2, C4.2, C5.2, C6.2, C7.2, C8.2, C9.2, C10.2, C11.2, C12.2, C13.2, C14.2, C15.2, C16.2, C17.2, C18.2, C19.2, C20.2, JMAIN.A2, JMAIN.A29, JMAIN.A55, M1A.2 (S), M1BF.2 (S), M1BG.2 (S), M2B2.2 (S), M2B3.2 (S), M3A.2 (S), M3BF.2 (S), M3BG.2 (S), R1L0.2, R1L1.2, R1L2.2, R1L3.2, R2.2, R2L0.2, R2L1.2, R2L2.2, R2L3.2, RDE.2, RI3.2, RI4.2, RIAF.2, RIAG.2, RIE.2, RIK.2, RIL.2, RIR.2, RIS4.2, RIU.2, RIX.2, RIY.2, RJAF.2, RJAG.2, RJK.2, RJL.2, RJR.2, RJU.2, RJX.2, RJY.2, RMAG.2, RNEE.2, RNN.2, RNS4.2, ROEE.2, RON.2, RPS4.2, RS6.2, RXE.2
W: M3.3 (D), Q2A.2, Q2K.2, Q2R.2, Q2U.2, Q2X.2, Q2Y.2
W#: M2.3 (D), Q1K.2, Q1R.2, Q1U.2, Q1X.2, Q1Y.2, Q3A.2
WA: JMAIN.A30, Q2A.1, Q3A.1
WR: JMAIN.A34, Q1R.1, Q2R.1
WU: JMAIN.A33, Q1U.1, Q2U.1
WX: JMAIN.A31, Q1X.1, Q2X.1
WY: JMAIN.A32, Q1Y.1, Q2Y.1
Wg: M2.1 (G), MIL.3 (D), MJL.1 (G), RIL.1
Wg#: M3.1 (G), MIL.1 (G), MJL.3 (D), RJL.1
X_A_F: M1NAF.3 (D), M2NAF.3 (D), MJAF.2 (S)
X_A_G: M1NAG.3 (D), M2NAG.3 (D), MJAG.2 (S)
X_L: M1NL.3 (D), M2NL.3 (D), MJL.2 (S)
Z: JMAIN.A43, M4.3 (D)
_d2: D2.2, R4.1
_d3: D3.2, R5.1
_sb: D5.2, Q3.1, R6.1
_sb#: D5.1, M1.2 (S), Q3.3
br_A: D1A.2, D2A.2, R3A.2
br_K: D1K.2, D2K.2, R1K.2
br_R: D1R.2, D2R.2, R1R.2
br_U: D1U.2, D2U.2, R1U.2
br_X: D1X.2, D2X.2, R1X.2
br_Y: D1Y.2, D2Y.2, R1Y.2
g#_B_F: M1BF.1 (G), M2BF.1 (G), Q1BF.3, R2BF.1
g#_B_G: M1BG.1 (G), M2BG.1 (G), Q1BG.3, R2BG.1
g_B_F: M3BF.1 (G), M4BF.1 (G), Q2BF.3, R1BF.2
g_B_G: M3BG.1 (G), M4BG.1 (G), Q2BG.3, R1BG.2
gl_A: M3A.1 (G), M4A.1 (G), Q3A.3, R1A.2
gr_A: M1A.1 (G), M2A.1 (G), Q2A.3, R2A.1
m_O_E_E: M1OEE.2 (S), M3OEE.3 (D)
phi: JMAIN.A40, M2MAG.1 (G), M2NAF.1 (G), M2NAG.1 (G), M2NL.1 (G), MAF.1 (G), ML.1 (G), Q1BF.1, Q1BG.1, Q1K.1, Q2BF.1, Q2BG.1, Q2K.1
qg_E: M2OEE.2 (S), M3OEE.2 (S), ME.3 (D)
r_X_E: M1XE.2 (S), M2XE.3 (D), M3XE.3 (D), M4XE.3 (D)
x_D_E: M1DE.2 (S), M2DE.3 (D)
x_N: M3ON.1 (G), MNN.3 (D), RNN.1
x_O_N: M1ON.3 (D), M2ON.3 (D), M3ON.2 (S)
x_S5: M1S5.2 (S), M2S5.3 (D)
x_S6: M1S6.2 (S), M2S6.3 (D)
x_S7: M1S7.2 (S), M2S7.3 (D)
x_S8: M1S8.2 (S), M2S8.3 (D)
x_S9: M1S9.2 (S), M2S9.3 (D)

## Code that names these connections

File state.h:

#ifndef STATE_H_                        // -*- C++ -*-
#define STATE_H_

#include <assert.h>
#include <string.h>
#include <map>

enum register_name_t { A, X, Y, U };

struct emitter_t {
    virtual void emit_byte(int address, int byte) = 0;
    virtual void emit_two(int address, int b1, int b2);
};


struct operand_t {
    operand_t(unsigned char n) :
        reg(-1), is_mem(false), value(n) { }
    operand_t(register_name_t r) :
        reg(r), is_mem(false), value(r) { }
    operand_t(const operand_t & other, bool m) :
        reg(other.reg), is_mem(m), value(other.value) { }
    int reg;
    bool is_mem;
    unsigned char value;
    operand_t mem() const { return operand_t(*this, true); }
};

enum condition_t {
    ALWAYS, NEVER, ALWAYS_R, NEVER_R, NZ, Z, NC, C
};

struct state_t {
    unsigned char reg[4];
    bool flag_C;
    bool flag_Z;
    unsigned char out_latch;
    void * stack[4];
    unsigned char mem[256];
    bool straight_through;              // Ignore branches.
    int executed;                       // Instruction count.
    int write_limit;
    emitter_t * emitter;

    // Only used for binary interpreter...
    signed char kreg;                   // 0...63 or -1 for none.
    int pc;                             // -1 for stop.

    void set64(int address, unsigned long v) {
        for (int i = 0; i != 8; ++i)
            mem[address - i] = v >> (i * 8);
    }
    unsigned long get64(int address) const {
        unsigned long result = 0;
        for (int i = 0; i != 8; ++i)
            result += (unsigned long) mem[address - i] << (i * 8);
        return result;
    }

    void step(int opcode);              // Binary interpreter.
    void run(const unsigned char program[256]);

    void account(int opcode, const operand_t & v);

    void account(int opcode);

    bool wanted(condition_t) const;

    unsigned char get(const operand_t & val) const {
        unsigned char v = val.reg < 0 ? val.value : reg[val.reg];
        return val.is_mem ? mem[v] : v;
    }
    unsigned char & get(register_name_t r) {
        return reg[r];
    }

    virtual void go(int start) = 0;

    int jump_take_number;
    int jump_source;
    const char * jump_target_name;
    std::map<std::string, int> jump_targets;

    void ADD(int opcode, const operand_t & val,
             bool cin = false, unsigned char flip = 0) {
        account(opcode, val);
        unsigned r = reg[A] + (get(val) ^ flip) + cin;
        flag_C = !!(r & 256);
        reg[A] = r;
        flag_Z = !(r & 255);
    }

    void ADD(const operand_t & val)  { ADD(0x40, val); }
    void ADDM(const operand_t & val) { ADD(val.mem()); }
    void ADC(const operand_t & val)  { ADD(0x48, val, flag_C); }
    void ADCM(const operand_t & val) { ADC(val.mem()); }

    void SUB(const operand_t & val)  { ADD(0x50, val, true,   255); }
    void SBC(const operand_t & val)  { ADD(0x58, val, flag_C, 255); }
    void SUBM(const operand_t & val) { SUB(val.mem()); }
    void SBCM(const operand_t & val) { SBC(val.mem()); }

    void AND(const operand_t & val) {
        account(0x70, val);
        reg[A] &= get(val);
        flag_Z = (reg[A] == 0);
        flag_C = true;
    }

    void ANDM(const operand_t & val) { AND(val.mem()); }

    void OR(const operand_t & val) {
        account(0x60, val);
        reg[A] |= get(val);
        flag_Z = (reg[A] == 0);
        flag_C = false;
    }

    void ORM(const operand_t & val) { OR(val.mem()); }

    void XOR(const operand_t & val) {
        account(0x68, val);
        reg[A] ^= get(val);
        flag_Z = (reg[A] == 0);
        flag_C = false;
    }

    void XORM(const operand_t & val) { XOR(val.mem()); }

    // FIXME: CMP

    void INC(register_name_t w, const operand_t & val) {
        account(0xe0 + w * 8, val);
        reg[w] = get(val) + 1;
        flag_Z = (reg[w] == 0);
    }

    void DEC(register_name_t w, const operand_t & val) {
        account(0xc0 + w * 8, val);
        reg[w] = get(val) - 1;
        flag_Z = (reg[w] == 0);
    }

    void INC(register_name_t r) { INC(r, r); }
    void DEC(register_name_t r) { DEC(r, r); }

    void INCM(register_name_t r, const operand_t & val) { INC(r, val.mem()); }
    void DECM(register_name_t r, const operand_t & val) { DEC(r, val.mem()); }

    void CLRC() {
        OR(A);
    }

    void SETC() {
        AND(A);
    }

    void LOAD(register_name_t ww, const operand_t & val) {
        account(0x80 + ww * 8, val);
        reg[ww] = get(val);
    }

    void LOADM(register_name_t ww, const operand_t & val) {
        LOAD(ww, val.mem());
    }

    void STA(const operand_t & val) {
        account(0xa4, val);
        assert(get(val) < write_limit);
        mem[get(val)] = reg[A];
    }

    void IN() {
        account(0xa0);
        // FIXME;
    }

    void OUT(const operand_t & val) {
        account(0xac, val);
        out_latch = get(val);
    }

    void push(void * x) {
        memmove(stack + 1, stack, 3 * sizeof stack[0]);
        stack[0] = x;
    }

    void * pop() {
        void * r = stack[0];
        memmove(stack, stack + 1, 3 * sizeof stack[0]);
        return r;
    }

    bool jump(condition_t cond, const char * name, int opcode = 0);

    bool retrn(condition_t cond) {
        account(0xa0 + cond * 4);
        return !straight_through && wanted(cond);
    }

    void extract_branches(int start);
};


#define JP(cond,label) do { if (jump(cond, #label, 32)) goto label; } while (0)
#define JMP(label) JP(ALWAYS,label)

#define JOIN2(x,y) x##y
#define JOIN(x,y) JOIN2(x,y)
#define RET_LABEL JOIN(return_label_,__LINE__)
#define call(label) do { push(&&RET_LABEL); goto label; RET_LABEL: ; } while (0)

#define CL(cond,label) do { if (jump(cond, #label)) call(label); } while (0)
#define CALL(label) CL(ALWAYS,label)

#define do_ret() do if (stack[0] == NULL) return; else goto *pop(); while (0)

#define RT(cond) do { if (retrn(cond)) do_ret(); } while (0)

#define RET() RT(ALWAYS_R)

struct print_emitter_t : emitter_t {
    print_emitter_t(FILE * f) : file(f) { }
    void emit_byte(int address, int byte);
    void emit_two(int address, int b1, int b2);

    FILE * file;
};

struct munge_emitter_t : emitter_t {
    munge_emitter_t(FILE * f, const char * p) :
        file(f), suffix(p) { }
    void emit_byte(int address, int byte);
    FILE * file;
    const char * suffix;
};


#endif

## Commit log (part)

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2018-02-18 In verilog model, single clock & give reads their own cycle.
2018-02-18 Two copies of the SP makes timing closure easier.
2018-02-18 Force use of a carry chain for decode effZ.
    Fix the nextPC...
2018-02-20 Some bugfixes. Move isolated parts of decode into fetch.
2018-03-04 Rework the SP handling.
2018-03-10 Tests.
2018-03-10 Initialize everything to keep isim happy and me unhappy.
2018-04-27 Various updates. verilog I/O interface.
2018-08-03 Vivado version
2021-02-03 Comments in rmsim.
2021-02-03 Vivado runaround.
2021-02-03 Fix cmp in the model.
2021-02-05 Add strong-drive latches instead of buffering.
2021-02-05 Reduce "infinite" to 1e8, makes spice happier.
2021-02-05 Keep spice happy.
2021-02-05 Purification design.
2021-02-07 Getting there with the new decode...
2021-02-07 Interminable gschem updates.
2021-02-07 Factor out the 4 way decode.
2021-02-07 Tidy up a bit. Fix carry-force.
2021-02-08 Symbols for everything, a big tidy-up & fixes.
2021-02-08 Getting testopdecode going...
2021-02-08 opdecode passes the current tests.
2021-02-08 Get the rest of the flags flying.
2021-02-08 Get testpcdecode going again.
2021-02-09 Dualize the OR strobe.
2021-02-09 Get testsp going again. Run tests from makefile.
2021-02-09 Update assembler for new coding.
2021-02-09 Working on getting univlite back.
2021-02-10 Feature complete again.
2021-02-10 Save a transistor on the alu.
2021-02-10 Lots of fix-ups.
2021-02-11 Fixes to the interpretation of the new opcodes.
2021-02-12 testadd flies again.
2021-02-12 testcall is back.
2021-02-12 testinc is back up.
2021-02-13 hazard flies.
2021-02-13 Sort out the ojump mess.
2021-02-13 Tidy ups.
2021-02-13 Simplify reset.
2021-02-14 Remove noverlap from address lines.
2021-02-14 Gray coded sp
2021-02-14 Replace xor with a sel for the ALU input inverter.
2021-02-14 Implement precharge/late read for the stack.
2021-02-15 Logic gate stacking in control & decode.
2021-02-15 Strobe & stack OUT.
2021-02-15 Renumber.
2021-02-15 Another one bites the dust.
2021-02-15 Two more tests; fix cmp.
2021-02-15 Simplify.
2021-02-16 Tidy.
2021-02-17 Use named nets more in bit. Tweak font sizes.
2021-02-17 Just write K on every cycle; no need to be precise.
2021-02-18 Integrated clock drive.
2021-02-18 Tweak the way pc & stack are handled.
2021-02-18 Big update to README.
2021-02-18 Use resistors not logic to mitigate the register read strobe hazard.
2021-02-19 README updates.
2021-02-19 Simplify the SP decode further.
2021-02-19 Routine tidy up.
2021-02-21 Major tidy up.
2021-02-23 Switch to dram.
2021-02-23 Move docs into their own directory.
2021-02-25 Switch DRAM to 8 by 8 decode.
2021-02-27 Simplify ROM, 64 byte board.
2021-02-27 Reset becomes flip-flop
2021-02-27 Get jiggy with pull-down diodes.
2021-02-27 Use 4T not 6T for the second flip-flop stage.
2021-02-27 Switch flip-flops completely to new latches.
2021-02-27 Kill dilatch entirely.
2021-02-27 Update counts.
2021-02-28 Name all nets connecting to 3 or more transistors.
2021-03-02 Move to 360p on the dram.
2021-03-02 Make the names of the basic switching elements generic.
2021-03-03 Flip NMOS over to FDV301N.
2021-03-03 Make the flip-flop stages robust against glitches.
2021-03-03 New dilatch, use it in FFs.
2021-03-03 Update ffs to use the new latches.
2021-03-03 Make DRAM precharge closer to threshold voltage. Gets DRAM working at lower Vto.
2021-03-03 Remove the remaining dlatches.
2021-03-03 Use dplatch where possible.
2021-03-04 Another round of tidy ups. Rebuild docs.
2021-03-04 Move to 200kHz for the main sim.
2021-03-04 Docs and net naming.
2021-03-05 Redo the ram decode. Add tests for ram and rom decode.
2021-03-05 Redo the ROM decode, the 8×8 only saved 1 transistor and was slow.
2021-03-05 Pmos on the clock input chain.
2021-03-05 Rename to W from D on the ram inputs
2021-03-05 Regen web pages
2021-03-05 Rebalance the ram fanout.
2021-03-06 Simulate at 250kHz, NX3008 for the PMOS.
2021-03-06 Web update, remove unused items.
2021-03-06 Add the full NXP model of the PDTC124.
2021-03-06 Get running with higher reverse capacitance on the NPN.
2021-03-07 Use 2sc4774 & separate resistor in the dram banks.
2021-03-07 Website update.
2021-03-08 Use a better transistor on the register readout.
2021-03-08 Flying at 3µs timing.
2021-03-09 Symbol for the strong pull resistor.
2021-03-10 Rearrange decode slightly
2021-03-12 Use a pot for the bias voltage.
2021-03-12 Fixup spice-load & verification.
2021-03-13 2.7V operation
2021-03-14 2.5v operation.
2021-03-15 Operation at 400kHz
2021-03-16 Add bling
2021-03-19 Minor updates and fixes. Remove unused files.
2021-03-20 Rename a couple of nets.
2021-03-20 Get rid of Z flipflop - generate Z off K instead.
2021-03-20 Rationalise some decode strobes.
2021-03-20 More rearrange.
2021-03-20 Convert C into a DE ff.
2021-03-21 Tidy up
2021-03-21 Name some nets.
2021-03-23 Strong I + BK flip flops.
2021-03-24 Rework decode somewhat.
2021-03-24 Simplify the half-adder.
2021-03-24 Adjust the ROM readout.
2021-03-25 Strong load resistors in the register file.
2021-03-25 Use an HBT on the stack sense line, speed up O lines, gives 2µs.
2021-03-29 Various tidy ups.
2021-04-02 Move bit & control into boards.
2021-04-02 Fix width of pads on the pci edge connector.
2021-04-02 Update symbols & footprints for the component selection we have.
    Nix old crap
2021-04-02 The layout starts.
2021-04-03 More layout. PC side done.
2021-04-03 DRAM refresh & address drivers.
2021-04-04 Swap in the refresh for instruction bit.
2021-04-04 Move ALU into place
2021-04-04 ALU resistors integrated
2021-04-04 HBTs rock.
2021-04-04 Instruction reg reintegrated.
2021-04-04 Ground tidy & mesh.
2021-04-05 Tidyup and silk screen.
2021-04-05 Fix via hole size.
2021-04-05 Top fill with ground. Bottom fill with vdd.
2021-04-05 Remove the noverlap cap.
2021-04-05 Trim board.
2021-04-07 Add bypass caps & tidy up.
2021-04-08 Remove some placebos.
2021-04-09 Shuffle a transistor out of the central column.
2021-04-10 Redo the central column.
2021-04-10 Rationalise somewhat
2021-04-14 Add a board layout image.
2021-05-08 Adjust docs.
2021-06-10 Starting on the control board
2021-06-10 Updating verilog to new instruction set
2024-01-10 Miller Rabin code
2024-01-10 Disassembler.
2024-01-10 Rationalise, rename to 'load' from 'mov'.
2024-01-10 Rationalise Value v. Operand.
2024-01-11 More rationalisation.
2024-01-12 Tidy up the disassemble interface.
2024-01-17 Minor changes.
2024-01-17 Add spice file handling and opdecode test.
2024-01-18 Tweaks; remove redundant binary
2024-01-18 Add alu and add tests.
    Add inline assertions & multi-variable iterator.
2024-01-18 Various decode tests
2024-01-19 Get lots of the verifier programs going.
2024-01-19 Lots more one-program.
2024-01-19 The two memory programs.
2024-01-19 Single program.
2024-01-19 Rename
2024-01-19 Verilog emitter.
2024-01-19 Final updates to the C++ code.
2024-01-19 Switch to lepton. Verilog updates.
2024-01-19 Move the old code out the way
2024-01-19 Remove dead files
2024-01-20 Add a test for the mem prefix and get it working.
    * The combinatorics was wrong.
    * Speed up a bit to meet timing.
2024-01-20 A round of simplification: The test instructions move to replace output-Y.
2024-01-20 Move QE down into decode.
2024-01-22 Regenerate documentation
2024-01-22 Add an explicit test for flipping memory bits.
2024-01-22 Tweak test timings a bit.
2024-01-22 Update ramdecode to clock the circuitry.
2024-01-25 Tighten testing a bit, fix pcdecode test.
2024-01-27 Tiny tweaks.
2024-01-27 Rust can do inline string interpolation of variables, when did that happen?
2024-01-27 Implicit prefixing for IN.
2024-01-27 Separate out the bias supply for now.
2024-02-05 Remove the zero constant from MR.
2024-02-05 Tweak labels.
2024-02-06 Abstract out prefix handling a bit.
2024-02-07 Prep notb using a normal bjt.
2024-02-08 Add miller clamps in a few places
2024-02-08 Update docs
2024-02-09 Parameter scan updates.
2024-02-10 Big update to the parameter scanner.
2024-02-10 Renumber some transistors.
2024-02-13 Align.
2024-02-13 Scan updates. Trim comments to what is useful.
2024-02-13 Caching expensive runs
2024-02-13 Scan updates.
2024-02-13 Change bias pot to 2.6v
2024-02-13 Sorting out 2.6V bias scan.
2024-02-14 Add some conditional return test cases.
2024-02-14 Change inc to test a RET C
2024-02-15 Switch to rload for the stack sense.
2024-02-15 Use saner resistors in the romio.
2024-02-17 Scan updatez.
2024-02-17 Change the bias transistor to BJT.
2024-02-18 Scanz.
2024-02-18 Separate dram resistors from others.
2024-02-19 Go to 10k on the dram base resistor.
2024-02-20 Scanz
2024-02-22 Add the diodes to the bit board.
2024-02-22 Alt ram sense
2024-02-27 Change the jfet model to level2
2024-02-27 Make the sense line less trigger happy.
2024-02-27 Remove the clock timing from the resistor scan.
2024-02-28 Fixes...
2024-02-28 Avoid glitches on vpush.
2024-02-29 Tweak the sense pulls.
2024-02-29 Go back to negative feedback on dramio.
2024-03-01 More verbose assert.
2024-03-02 Include the refresh counter in the verification.
2024-03-02 Tighten up due to refresh check.
2024-03-02 Tidy up.
2024-03-02 Add memory check.
2024-03-03 Lower the feedback resistor.
2024-03-03 Reduce the clock delay.
2024-03-05 Redo the sense line bias resistor.
2024-03-05 Rationalise resistor scans.
2024-03-05 Use diodes logic on the register read.
2024-03-05 Tweak pulls.
2024-03-05 Try bat42, and speed up stack strobes.
2024-03-06 Stack checking.
2024-03-07 This one looks like the sweet spot
2024-03-08 Try J309, it seems very available
2024-03-08 Use nominal Vss on ramdecode test.
2024-03-09 Weaken register resistors.
2024-03-11 Recover clock edge instead of guessing.
2024-03-13 Tweaks.
2024-03-15 Simplify ram interface.
2024-03-15 Convert dram write strobes to pmos.
2024-03-16 Resistor tweak, shuffle co-ordinates.
2024-03-17 Use a better diode model.
2024-03-18 JFET tidy.
2024-03-18 Move the dram write logic to the second stage of the interface.
2024-03-21 Tweak resistors.
2024-03-21 Go to 470pF.
2024-03-25 Remove the obsolete resistors. And thermals to vias.
2024-03-25 Make the double diodes sot23 footprint.
2024-03-25 Labels.
2024-03-25 Weaken a pull-down.
2024-03-26 Simplify the conditional handling.
2024-03-27 Speed up the increment carry chains.
2024-03-27 Redo the refresh; use the ALU instead of the increment, and put it into the register bank.
2024-03-29 Speed up A reg transitions.
2024-03-29 Speed up the ROM output.
2024-03-29 Swap ret and misc instructions.
2024-03-30 Restore a pull resistors, it helps.
2024-03-30 Completely model the K register & use the STA encoding that doesn't read back.
2024-03-30 Add test for conditional critical paths.
2024-03-30 Speed some strobes that are critical to the carry chain.
2024-03-31 Web page update.
2024-03-31 Try mosfets not bjt for the stack write.
2024-04-01 Strong resistors there are useless.
2024-04-01 Pmos for the strobe again....
2024-04-01 Adjust check sample timing.
2024-04-01 Differential sampling where possible.
2024-04-01 Speed up the carry launch.
2024-04-01 Tweak.
2024-04-02 Fix the hazard in ret test.
2024-04-02 Web page update
2024-04-02 Go to 620p for the DRAM.
2024-04-03 Check the mosfet transconductance.
2024-04-03 Test a glitch case.
2024-04-03 Remove 'mem' test, its covered by other things.
2024-04-04 Use release build of the tooling.
2024-04-11 Be sensible on the MW strobe.
2024-04-18 Simplify out strobe.
2024-04-18 Exclude dram from a generic test!
2026-03-12 Test touch-ups.
2026-03-12 Add randomization to search order.
2026-03-13 Update test bounds.
2026-03-13 Starting on kicad bit board layout
2026-03-14 Bit board mostly routed.
2026-03-15 Silkscreen sorted, and a little DRC clean-up.
2026-03-15 Separate the double diodes.
2026-03-15 Route the bit board connector. DRC clean.
2026-03-15 Tidy silkscreen a bit.
2026-03-16 Correct led polarity.
2026-03-16 Optimize for base board routing.
2026-03-16 Adjust footprints before renaming
2026-03-16 Rename footprints to be more systematic.
2026-03-17 Start on control board.
